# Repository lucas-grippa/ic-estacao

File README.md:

# Estação Didática Automatizada Controlada por Arduino

[Video do projeto](https://www.youtube.com/watch?v=upOcH8F2Osk)

## Resumo do projeto

Sistemas automatizados representam a grande maioria dos processos industriais e crescem em ritmo acelerado em todos os setores da sociedade, assim como a o desenvolvimento de software de modo geral, praticamente onipresente no cotidiano comum. Dada a importância da automação, a formação de profissionais altamente capacitados para trabalhar nesses ambientes se tornou meta em vários países.<br/>
Uma estratégia de ensino mais eficiente e moderna pode ser implementada por meio de uma abordagem que exija mais iniciativa e atividade prática do aluno. Este conceito de "aprender na prática" se torna particularmente importante para estudantes de engenharia, já que os profissionais atuando nessa área serão confrontados com problemas práticos a todo momento. O que torna desenvolvimento de ferramentas que possibilitem a realização de exercícios desta natureza fundamental.<br/>
O objetivo deste trabalho foi projetar e construir uma estação automatizada didática de pequeno porte e baixo custo, em nível software e hardware, utilizando tecnologias de hardware e software open source como a plataforma Arduino (microcontrolador) e o freeRTOS (sistema operacional de tempo real), não tão convencionais em meio acadêmico.<br/>
Os resultados obtidos a partir da construção do protótipo totalmente funcional e de duas camadas de software, firmware e interface gráfica, mostram que o uso dessas tecnologias possuem um grande potencial para o desenvolvimento de dispositivos didáticos de baixo custo, relacionados ao ensino de programação, automação de sistemas e software embarcado, contribuindo assim para a democratização do conhecimento em tais áreas.<br/> 

*Foto do protótipo construido*

## Code Station

A interface de usuário, chamada de Code Station, foi desenvolvida utilizando a linguagem JavaScript e o framework Electron que permite a construção de aplicações desktop nativas (MacOS, Windows e Linux) utilizando tecnologias de desenvolvimento web como JavaScript, HTML e CSS.<br/> 

*Interface do CodeStation*

A funcionalidade desta interface é permitir com que o usuário desenvolva apenas um algoritmo de controle sem que haja a necessidade em se preocupar com configurações, calibragem, threads e sem que seja preciso utilizar qualquer tipo de conhecimento avançado na linguagem de programação c++, além disso a interface ainda exibe todas as informações necessárias (funções e parâmetros), para que seja feito o controle da estação, sobre cada dispositivo disponível no projeto. 
Para gerar um código que possa ser executado na estação automatizada basta que o usuário escreva um algoritmo utilizando as funções disponíveis dos dispositivos e clique em salvar, fazendo isso o software Code Station insere no código do usuário todas as bibliotecas e configurações necessárias para que tudo seja executado de forma paralela em um RTOS (Real Time Operating System) instalado no microcontrolador da estação, gerando um arquivo final com extensão .ino, que pode ser carregado para o Arduino (microcontrolador) que controla a estação, utilizando a IDE Arduino. 

## Firmware

A camada de software do projeto que tem funções semelhantes às de um firmware em sistemas embarcados, é composta por dois tipos de elementos: 

### Bibliotecas individuais para cada dispositivo da estação 

Para cada dispositivo que pode ser controlado na estação (atuadores e sensores) foi desenvolvida uma biblioteca (utilizando a linguagem c++) própria que tem como funções: configurar e calibrar cada dispositivo de forma automática (sem que o usuário final precise faze-lo) e abstrair as funções de controle e leitura de dados, de forma que o usuário final possa desenvolver um algoritmo que faça todo o controle da estação utilizando apenas estruturas básicas da linguagem C (condicionais, loops, variáveis simples) e as funções de controle e leitura disponíveis nas bibliotecas.<br/>
As bibliotecas são divididas em atuadores e sensores:<br/> 

* Atuadores
    * Esteira
    * Atuadores lineares DC
    * Atuador linear de passo (carimbo)
    * Atuador circular (reservatório giratório)
    * Display LCD

* Sensores
    * Sensor de barreira
    * Sensor de cor
    * Sensor "switch" (fazem parte dos atuadores)
    * Sensor ultrassônico

### Sistema operacional de tempo real (RTOS) 

O sistema operacional de tempo real escolhido para o projeto foi o freeRTOS já que este RTOS é projetado para ser utilizado em microcontroladores, exigindo pouca memória do sistema para funcionar, além disso o software possui licença open source. 
O uso de um RTOS foi necessário para o projeto já que o sistema precisa executar uma série de tarefas de forma paralela para que o usuário final possa escrever um algoritmo de forma simples e estruturada. Tal arquitetura foi alcançada utilizando o recurso de 'multitasking' controlado pelo RTOS.<br/>
O sistema possui 6 threads sendo executadas de forma "simultânea".<br/> 
Vale ressaltar aqui que não é possível executar threads de forma realmente paralela utilizando um Arduino, já que o processador do dispositivo possui apenas um núcleo físico, dessa forma o RTOS "simula" o efeito multitasking via software, utilizando um contexto privado dedicado de RAM e um processo de "scheduling" para executar cada tarefa.<br/> 
As threads utilizadas para o controle da estação são:<br/>

* TaskSensorMonitoring 
* TaskUltrasonicSensorMonitoring
* TaskActuatorControl
* TaskConveyorBeltControl
* TaskStationControl
* TaskDisplayLCD

## License
MIT © [Lucas Grippa](https://github.com/lucas-grippa)

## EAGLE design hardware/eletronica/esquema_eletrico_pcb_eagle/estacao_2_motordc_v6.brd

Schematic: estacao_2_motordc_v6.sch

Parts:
CI-AT1-AT2, CI-AT3: L293D; DIL16
CI-M1, CI-M2: ULN2003AN; DIL16
MEGA_PRO_MINI1: MEGA_PRO_MINI
PIN-AT1, PIN-AT2: PINHD-1X2; 1X02
PIN-AT3: PINHD-1X4; 1X04
PIN-LASER1, PIN-LASER2, PIN-LASER3, PIN-LASER4, PIN-LASER5: PINHD-1X3; 1X03
PIN-LCD_16X2: PINHD-1X12; 1X12
PIN-LDR1, PIN-LDR2, PIN-LDR3, PIN-LDR4, PIN-LDR5: PINHD-1X2; 1X02
PIN-M1, PIN-M2: PINHD-1X5; 1X05
PIN-S1-ULTRASSONICO, PIN-S2-COR-1: PINHD-1X4; 1X04
PIN-S2-COR-2: PINHD-1X3; 1X03
POWER_SUPPLY_PINS: PINHD-1X4; 1X04
R1, R2, R3, R4, R5, R7, R8, R9, R10, R11, R12, R13, R14, R15: 10K; 0204/7
R6: 1K; 0204/7
S-AVANÇO-AT1, S-AVANÇO-AT2, S-AVANÇO-AT3: PINHD-1X2; 1X02
S-POSICAO-RESERVATORIO, S-POSICAO-RESERVATORIO1, S-POSICAO-RESERVATORIO2: PINHD-1X2; 1X02
S-RECUO-AT1, S-RECUO-AT2, S-RECUO-AT3: PINHD-1X2; 1X02

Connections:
2: CI-M1.1 (I1), MEGA_PRO_MINI1.2
3: CI-M1.2 (I2), MEGA_PRO_MINI1.3
4: CI-M1.3 (I3), MEGA_PRO_MINI1.4
5: CI-M1.4 (I4), MEGA_PRO_MINI1.5
5V: CI-AT1-AT2.1 (1-2EN), CI-AT1-AT2.9 (3-4EN), CI-AT1-AT2.16 (VCC1), CI-AT3.1 (1-2EN), CI-AT3.9 (3-4EN), CI-AT3.16 (VCC1), MEGA_PRO_MINI1.5V, PIN-S1-ULTRASSONICO.1, PIN-S2-COR-1.1, R1.2, R2.2, R3.2, R4.2, R5.2, S-AVANÇO-AT1.1, S-AVANÇO-AT2.1, S-AVANÇO-AT3.1, S-POSICAO-RESERVATORIO.1, S-POSICAO-RESERVATORIO1.1, S-POSICAO-RESERVATORIO2.1, S-RECUO-AT1.1, S-RECUO-AT2.1, S-RECUO-AT3.1
6: CI-M2.1 (I1), MEGA_PRO_MINI1.6
7: CI-M2.2 (I2), MEGA_PRO_MINI1.7
8: CI-M2.3 (I3), MEGA_PRO_MINI1.8
9: CI-M2.4 (I4), MEGA_PRO_MINI1.9
10: CI-AT1-AT2.15 (4A), MEGA_PRO_MINI1.10
11: CI-AT1-AT2.10 (3A), MEGA_PRO_MINI1.11
12: CI-AT1-AT2.2 (1A), MEGA_PRO_MINI1.12
13: CI-AT1-AT2.7 (2A), MEGA_PRO_MINI1.13
16: CI-AT3.15 (4A), MEGA_PRO_MINI1.16(TX2)
17: CI-AT3.10 (3A), MEGA_PRO_MINI1.17(RX2)
18: CI-AT3.2 (1A), MEGA_PRO_MINI1.18(TX1)
19: CI-AT3.7 (2A), MEGA_PRO_MINI1.19(RX1)
22: MEGA_PRO_MINI1.22, PIN-LASER1.1
23: MEGA_PRO_MINI1.23, PIN-LASER2.1
24: MEGA_PRO_MINI1.24, PIN-LASER3.1
25: MEGA_PRO_MINI1.25, PIN-LASER4.1
26: MEGA_PRO_MINI1.26, PIN-LASER5.1
27: MEGA_PRO_MINI1.27, PIN-S2-COR-2.1
28: MEGA_PRO_MINI1.28, PIN-S2-COR-2.2
29: MEGA_PRO_MINI1.29, PIN-S2-COR-1.2
30: MEGA_PRO_MINI1.30, PIN-S2-COR-1.4
31: MEGA_PRO_MINI1.31, PIN-S2-COR-1.3
32: MEGA_PRO_MINI1.32, PIN-LCD_16X2.10
33: MEGA_PRO_MINI1.33, PIN-LCD_16X2.9
34: MEGA_PRO_MINI1.34, PIN-LCD_16X2.8
35: MEGA_PRO_MINI1.35, PIN-LCD_16X2.7
36: MEGA_PRO_MINI1.36, PIN-LCD_16X2.6
37: MEGA_PRO_MINI1.37, PIN-LCD_16X2.4
38: MEGA_PRO_MINI1.38, R7.1, S-AVANÇO-AT1.2
39: MEGA_PRO_MINI1.39, R9.1, S-RECUO-AT1.2
40: MEGA_PRO_MINI1.40, R10.1, S-AVANÇO-AT2.2
41: MEGA_PRO_MINI1.41, R11.1, S-RECUO-AT2.2
42: MEGA_PRO_MINI1.42, R12.1, S-AVANÇO-AT3.2
43: MEGA_PRO_MINI1.43, R13.1, S-RECUO-AT3.2
44: MEGA_PRO_MINI1.44, R8.1, S-POSICAO-RESERVATORIO.2
45: MEGA_PRO_MINI1.45
46: MEGA_PRO_MINI1.46, R15.1, S-POSICAO-RESERVATORIO2.2
47: MEGA_PRO_MINI1.47, R14.1, S-POSICAO-RESERVATORIO1.2
+5V: CI-AT3.8 (VCC2), PIN-LASER1.2, PIN-LASER2.2, PIN-LASER3.2, PIN-LASER4.2, PIN-LASER5.2, PIN-LCD_16X2.2, PIN-LCD_16X2.11, POWER_SUPPLY_PINS.4
+12V: CI-AT1-AT2.8 (VCC2), CI-M1.9 (CD+), CI-M2.9 (CD+), MEGA_PRO_MINI1.VIN., PIN-M1.5, PIN-M2.5, POWER_SUPPLY_PINS.1
A0: MEGA_PRO_MINI1.A0, PIN-LDR1.1, R1.1
A1: MEGA_PRO_MINI1.A1, PIN-LDR2.2, R2.1
A2: MEGA_PRO_MINI1.A2, PIN-LDR3.2, R3.1
A3: MEGA_PRO_MINI1.A3, PIN-LDR4.2, R4.1
A4: MEGA_PRO_MINI1.A4, PIN-LDR5.2, R5.1
AT1-1: CI-AT1-AT2.3 (1Y), PIN-AT1.1
AT1-2: CI-AT1-AT2.6 (2Y), PIN-AT1.2
AT2-1: CI-AT1-AT2.11 (3Y), PIN-AT2.1
AT2-2: CI-AT1-AT2.14 (4Y), PIN-AT2.2
AT3-1: CI-AT3.3 (1Y), PIN-AT3.1
AT3-2: CI-AT3.6 (2Y), PIN-AT3.2
AT3-3: CI-AT3.11 (3Y), PIN-AT3.3
AT3-4: CI-AT3.14 (4Y), PIN-AT3.4
ECHO: MEGA_PRO_MINI1.21, PIN-S1-ULTRASSONICO.3
GND: CI-AT1-AT2.4 (GND1), CI-AT1-AT2.5 (GND2), CI-AT1-AT2.12 (GND4), CI-AT1-AT2.13 (GND3), CI-AT3.4 (GND1), CI-AT3.5 (GND2), CI-AT3.12 (GND4), CI-AT3.13 (GND3), CI-M1.8 (GND), CI-M2.8 (GND), MEGA_PRO_MINI1.GND., MEGA_PRO_MINI1.GND..., PIN-LASER1.3, PIN-LASER2.3, PIN-LASER3.3, PIN-LASER4.3, PIN-LASER5.3, PIN-LCD_16X2.1, PIN-LCD_16X2.5, PIN-LCD_16X2.12, PIN-LDR1.2, PIN-LDR2.1, PIN-LDR3.1, PIN-LDR4.1, PIN-LDR5.1, PIN-S1-ULTRASSONICO.4, PIN-S2-COR-2.3, POWER_SUPPLY_PINS.2, POWER_SUPPLY_PINS.3, R6.2, R7.2, R8.2, R9.2, R10.2, R11.2, R12.2, R13.2, R14.2, R15.2
M1-1: CI-M1.16 (O1), PIN-M1.1
M1-2: CI-M1.15 (O2), PIN-M1.2
M1-3: CI-M1.14 (O3), PIN-M1.3
M1-4: CI-M1.13 (O4), PIN-M1.4
M2-1: CI-M2.16 (O1), PIN-M2.1
M2-2: CI-M2.15 (O2), PIN-M2.2
M2-3: CI-M2.14 (O3), PIN-M2.3
M2-4: CI-M2.13 (O4), PIN-M2.4
unnamed: PIN-LCD_16X2.3, R6.1
TRIG: MEGA_PRO_MINI1.20, PIN-S1-ULTRASSONICO.2

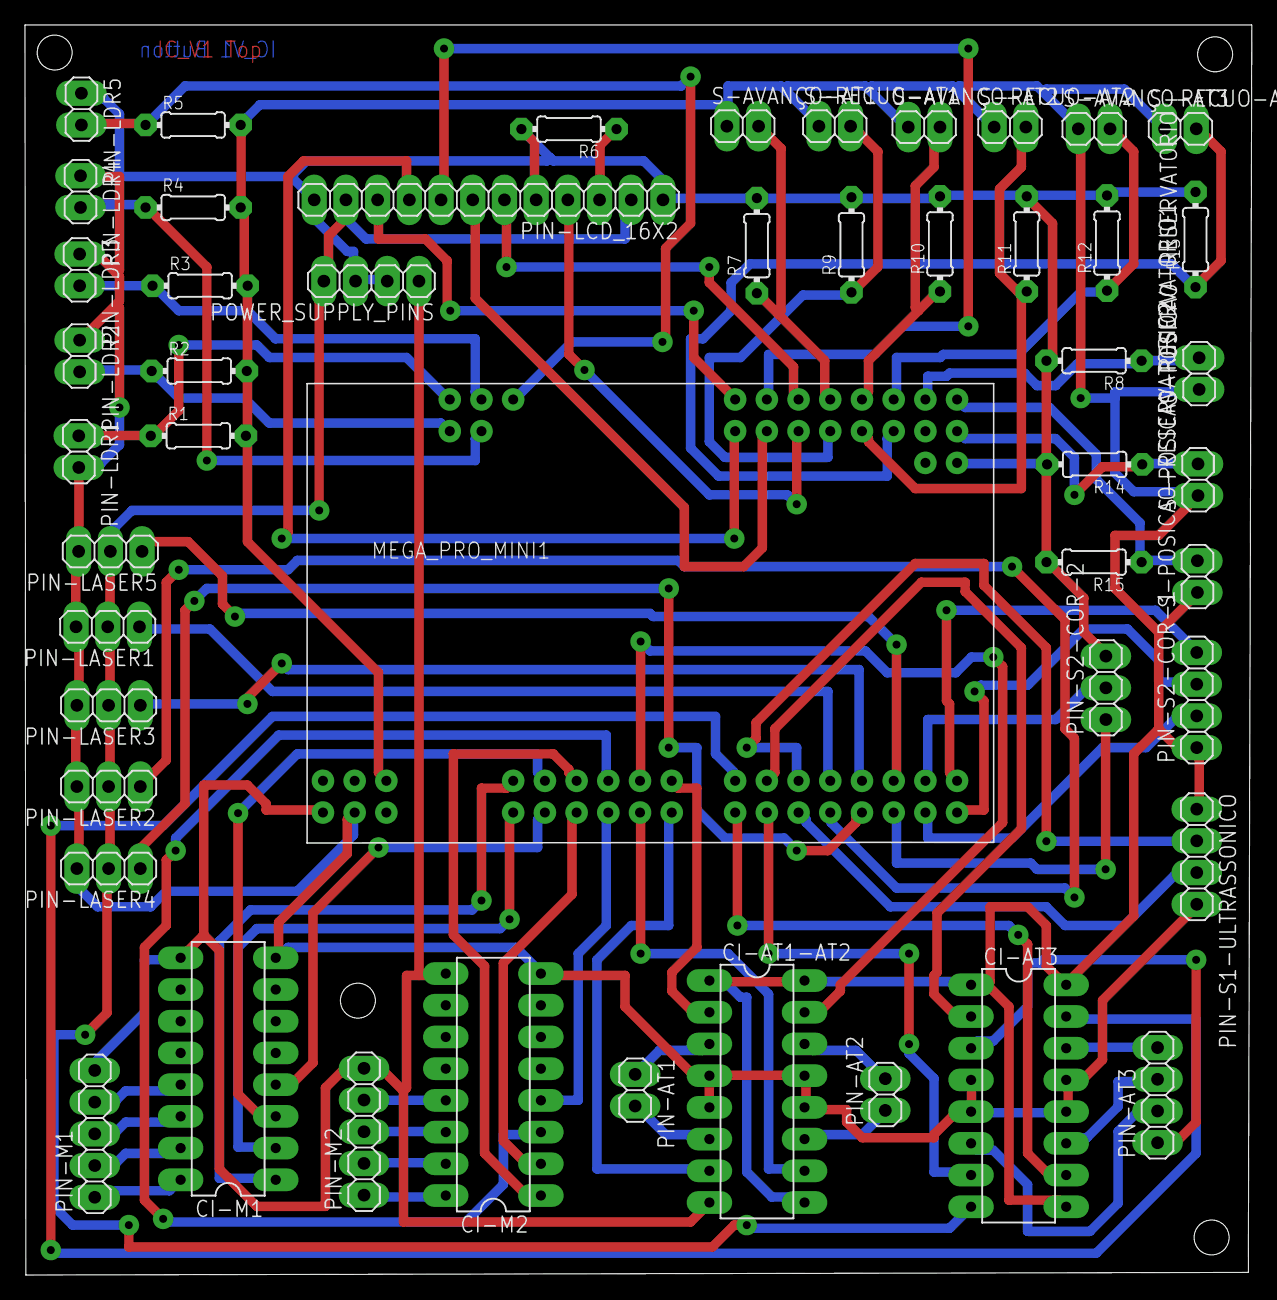
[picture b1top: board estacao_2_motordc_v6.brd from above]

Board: 2 copper layers, 98.3 x 100.1 mm, 49 parts (0 on the bottom side), 69 nets.

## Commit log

2017-08-17 Biblioteca BarrierSensor criada
2017-08-17 .gitignore adicionado
2017-08-17 rename to BarrierSensor
2017-08-22 BarrierSensor v1.0 terminada
2017-08-22 library.properties adicionada a BarrierSensor
2017-08-23 ColorSensor library feita
2017-08-23 UltrasonicSensor library feita
2017-08-24 SwitchSensor library feita
2017-08-24 ConveyorBelt library feita
2017-08-24 LinearDCActuator library feita
2017-08-25 LinearStepActuator library feita
2017-08-25 CircularActuator library feita
2017-08-30 freeRTOS libraries feitas e minor bug fixes
2017-08-30 Testes das bibliotecas feitos
2017-09-10 major libraries bug fixes, libraries-tests adicionado, code-station electron-react app adicionado
2017-09-10 code station readme v 0.0
2017-09-11 redux e device-item components adicionados
2017-09-12 devices component feito
2017-09-15 monaco editor adicionado
2017-09-16 initialContent adicionado
2017-09-19 open e save buttons adicionados
2017-09-26 organização de arquivos
2017-09-27 readme update
2017-09-27 documentação adicionada
2017-11-12 esquema eletrico adicionado
2017-11-12 reorganização dos arquivos
2017-11-12 modelo 3D adicionado
2017-11-12 cad adicionado
2018-03-08 Imagens do projeto adicionadas
2018-03-08 Imagem do CodeStation adicionada ao README
2018-03-08 Foto da estacao adicionada
2018-03-08 Foto da estacao adicionada ao README
2018-03-08 Atualização do README
